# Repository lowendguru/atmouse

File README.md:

# Introduction to ATmouse

This device is intended to be an assistive technology solution for computer users whom due to disability or physical condition find it difficult to use a regular mouse but are still able to push buttons. Users with Parkinson's disease, any tremor related condition, cerebral palsy and many other conditions that interfere with the users' ability to make precise hand movements.

The device is based on the Arduino Pro Micro (Leonardo compatible) and thus is a plug and play input device, meaning that it will be recognized as a USB mouse without the need of any additional drivers.

The device has a total of 13 buttons and 3 LED lights. The user can press buttons to:
- Move the mouse pointer (up, down, left, right)
- Left click
- Double left click
- Right click
- Hold left click
- Middle button click
- Hold middle button click
- Scroll wheel (up and down)
- Change the mouse movement speed between 3 different settings.

# Instructions

Print the 3 plastic parts (front case, back case, buttons array).
Etch or mill the PCB. This is a single sided PCB board and the tracks only use the "bottom" layer. Ignore the "top" layer of the Eagle design, but use wire jumpers to make the connections seen in the "top" layers.
Solder all electrical components to the PCB according to the Eagle design.
Upload the .ino sketch to the Pro Mini using Arduino IDE (Leonardo board settings).

Assemble the device. Start by placing the cover facing down on a table.
Then put the buttons array inside the sockets.
Make sure the USB cable is connected to the Pro Micro. Then place the PCB, the 5mm LEDs will fit inside their sockets and this will align the whole board into the front case.
Finally place the back case to close. You may have to glue the back case (as there are no screw holes in this version).
Optionally, you can use some pieces Polyurethane foam or similar material between the buttons array and the PCB, and also between the PCB and the back case for a tighter fit.

# Bill of materials

13 - 6mm push buttons
13 - 10k resistors
3 - 5mm LED
3 - 1k resistors
1 - PCB board 200x150mm (1 sided)
1 - Arduino Pro Micro
1 - Mini-USB cable
1 - Front case (3d printed)
1 - Back case (3d printed)
1 - Buttons array (3d printed)
Some foam rubber, Polyurethane foam or similar material (for a tighter fit)
Some strong glue (no screws yet, sorry)

# Demo video

https://www.youtube.com/watch?v=QU9dcgiuyGs

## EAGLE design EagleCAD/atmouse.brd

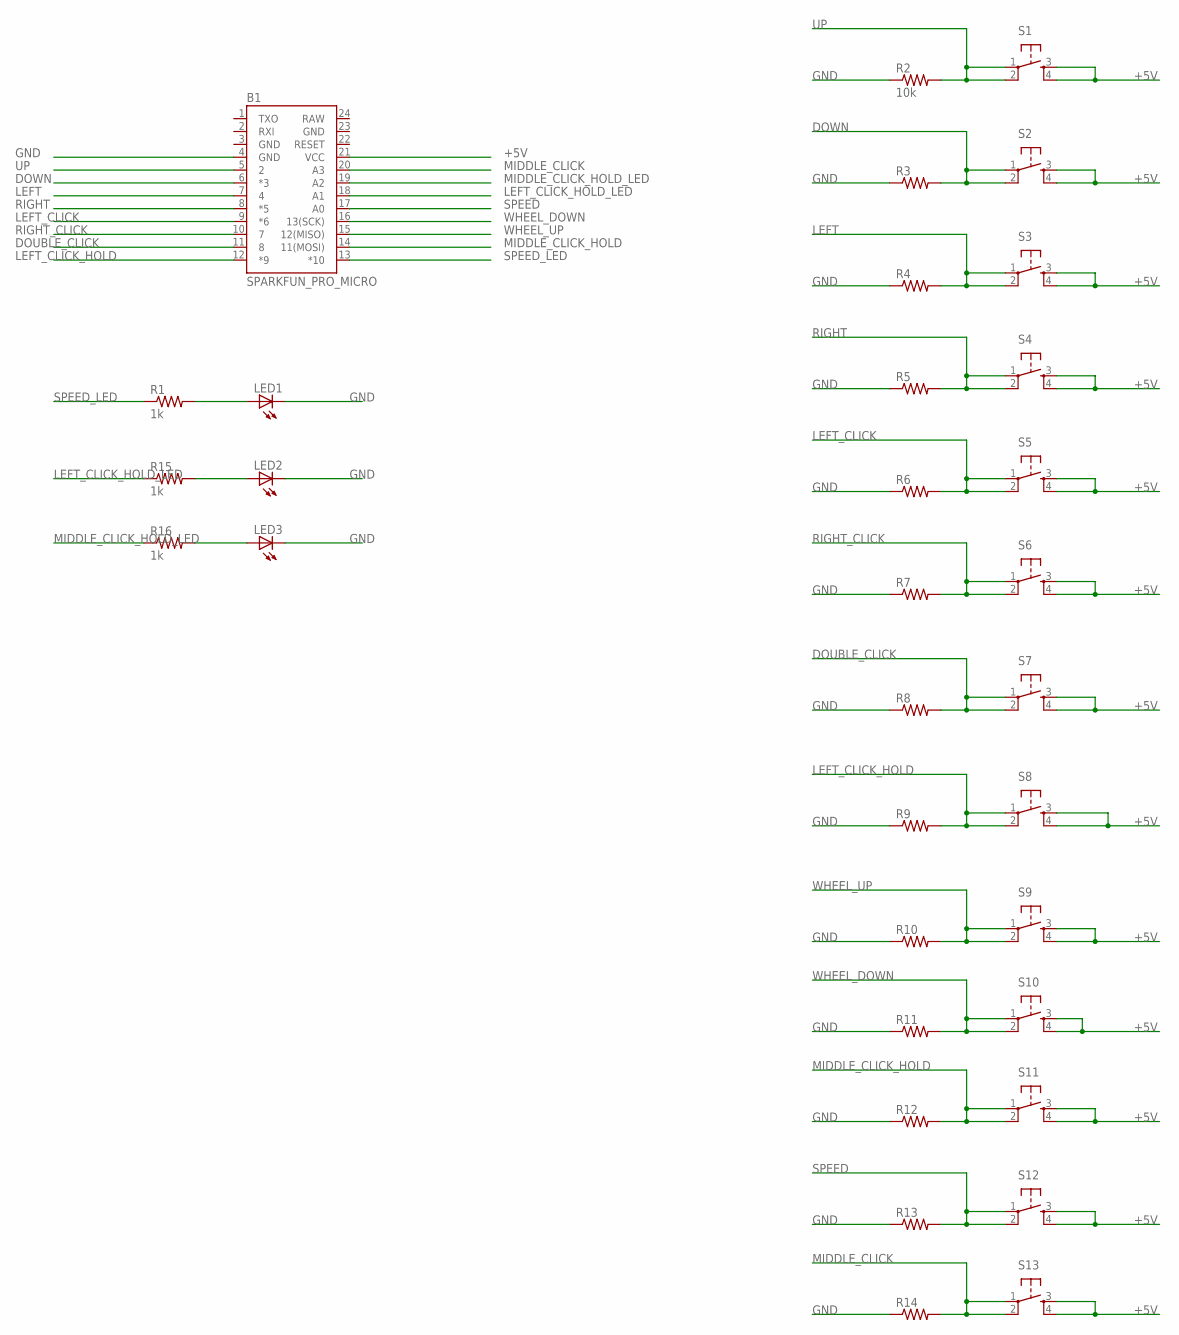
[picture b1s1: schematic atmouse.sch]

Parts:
B1: SPARKFUN_PRO_MICRO
LED1, LED2, LED3: LED5MM
R1, R15, R16: 1k; AXIAL-0.5
R2: 10k; AXIAL-0.5
R3, R4, R5, R6, R7, R8, R9, R10, R11, R12, R13, R14: RESISTORPTH-1/2W; AXIAL-0.5
S1, S2, S3, S4, S5, S6, S7, S8, S9, S10, S11, S12, S13: TAC_SWITCHPTH; TACTILE-PTH

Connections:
+5V: B1.21 (VCC), S1.3, S1.4, S2.3, S2.4, S3.3, S3.4, S4.3, S4.4, S5.3, S5.4, S6.3, S6.4, S7.3, S7.4, S8.3, S8.4, S9.3, S9.4, S10.3, S10.4, S11.3, S11.4, S12.3, S12.4, S13.3, S13.4
DOUBLE_CLICK: B1.11 (8), R8.P$2 (2), S7.1, S7.2
DOWN: B1.6 (*3), R3.P$2 (2), S2.1, S2.2
GND: B1.3 (GND), B1.4 (GND), B1.23 (GND), LED1.K (C), LED2.K (C), LED3.K (C), R2.P$1 (1), R3.P$1 (1), R4.P$1 (1), R5.P$1 (1), R6.P$1 (1), R7.P$1 (1), R8.P$1 (1), R9.P$1 (1), R10.P$1 (1), R11.P$1 (1), R12.P$1 (1), R13.P$1 (1), R14.P$1 (1)
LEFT: B1.7 (4), R4.P$2 (2), S3.1, S3.2
LEFT_CLICK: B1.9 (*6), R6.P$2 (2), S5.1, S5.2
LEFT_CLICK_HOLD: B1.12 (*9), R9.P$2 (2), S8.1, S8.2
LEFT_CLICK_HOLD_LED: B1.18 (A1), R15.P$1 (1)
MIDDLE_CLICK: B1.20 (A3), R14.P$2 (2), S13.1, S13.2
MIDDLE_CLICK_HOLD: B1.14 (11(MOSI)), R12.P$2 (2), S11.1, S11.2
MIDDLE_CLICK_HOLD_LED: B1.19 (A2), R16.P$1 (1)
unnamed: LED1.A, R1.P$2 (2)
unnamed: LED2.A, R15.P$2 (2)
unnamed: LED3.A, R16.P$2 (2)
RAW: B1.24 (RAW)
RIGHT: B1.8 (*5), R5.P$2 (2), S4.1, S4.2
RIGHT_CLICK: B1.10 (7), R7.P$2 (2), S6.1, S6.2
SPEED: B1.17 (A0), R13.P$2 (2), S12.1, S12.2
SPEED_LED: B1.13 (*10), R1.P$1 (1)
UP: B1.5 (2), R2.P$2 (2), S1.1, S1.2
WHEEL_DOWN: B1.16 (13(SCK)), R11.P$2 (2), S10.1, S10.2
WHEEL_UP: B1.15 (12(MISO)), R10.P$2 (2), S9.1, S9.2

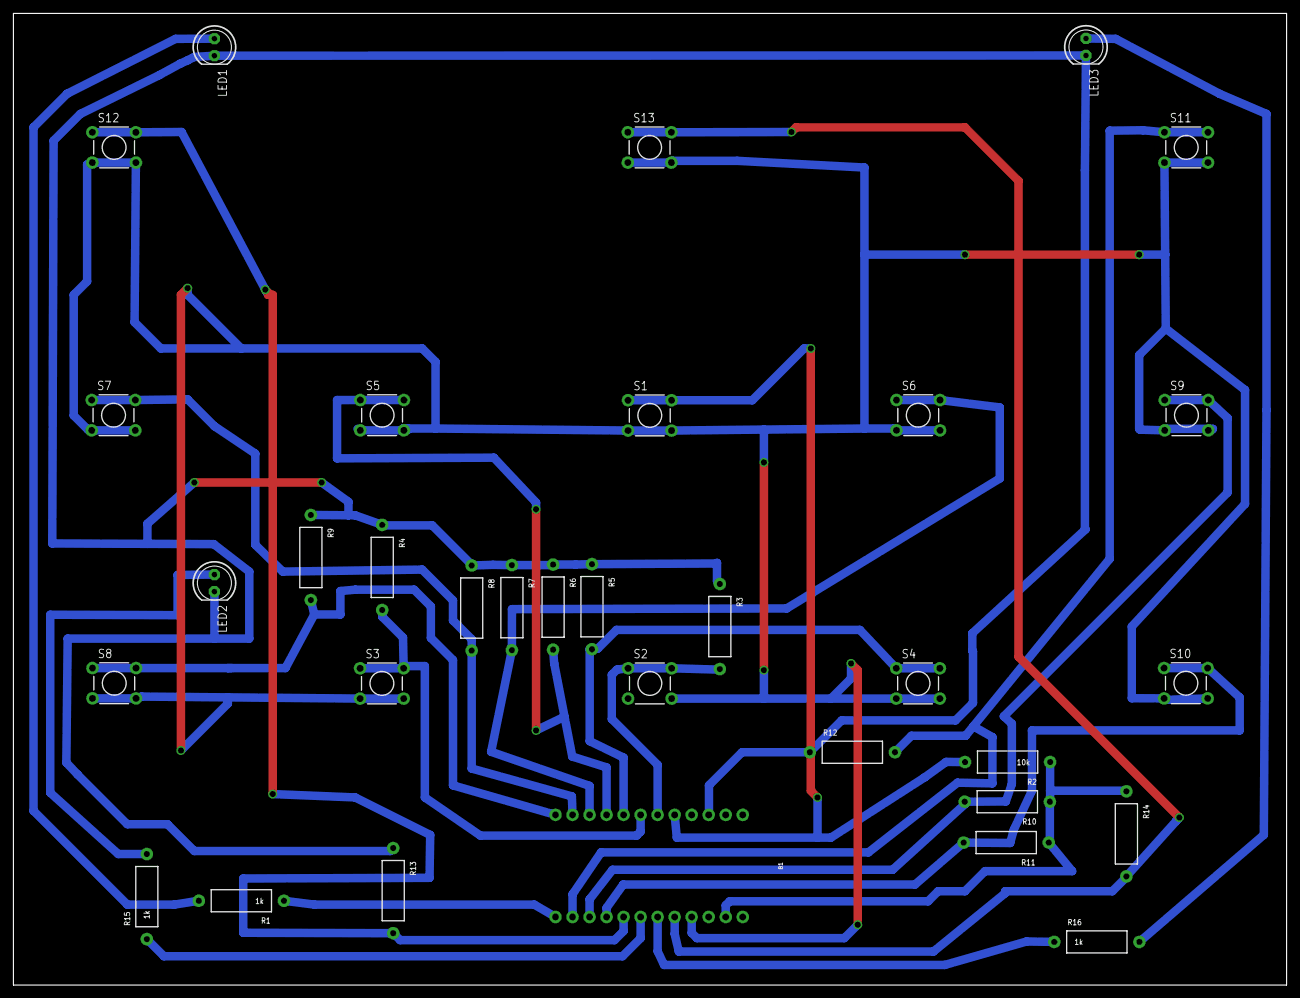
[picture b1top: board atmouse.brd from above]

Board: 2 copper layers, 190.0 x 145.0 mm, 33 parts (0 on the bottom side), 21 nets.

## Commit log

2023-07-28 adding arduino mouse library

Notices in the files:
parts and their libraries:
SparkFun-Boards: Licensing: Creative Commons ShareAlike 4.0 International - https://creativecommons.org/licenses/by-sa/4.0
